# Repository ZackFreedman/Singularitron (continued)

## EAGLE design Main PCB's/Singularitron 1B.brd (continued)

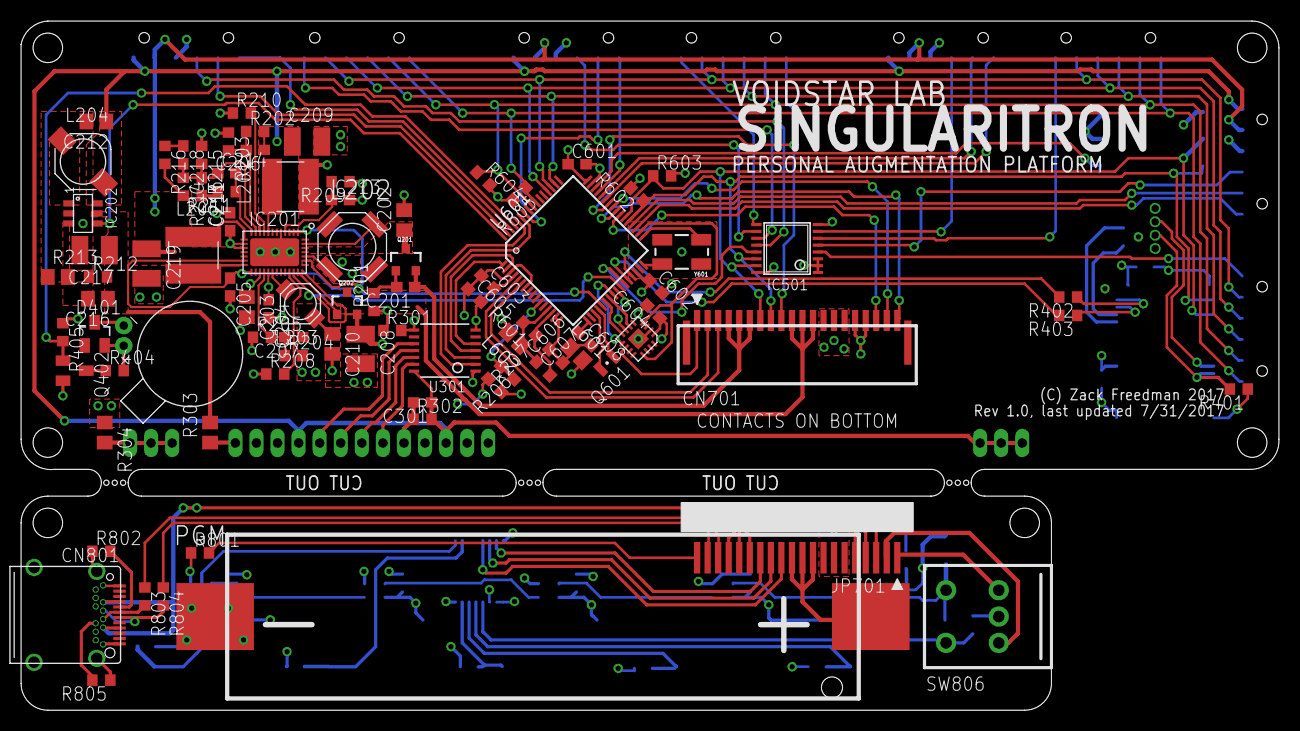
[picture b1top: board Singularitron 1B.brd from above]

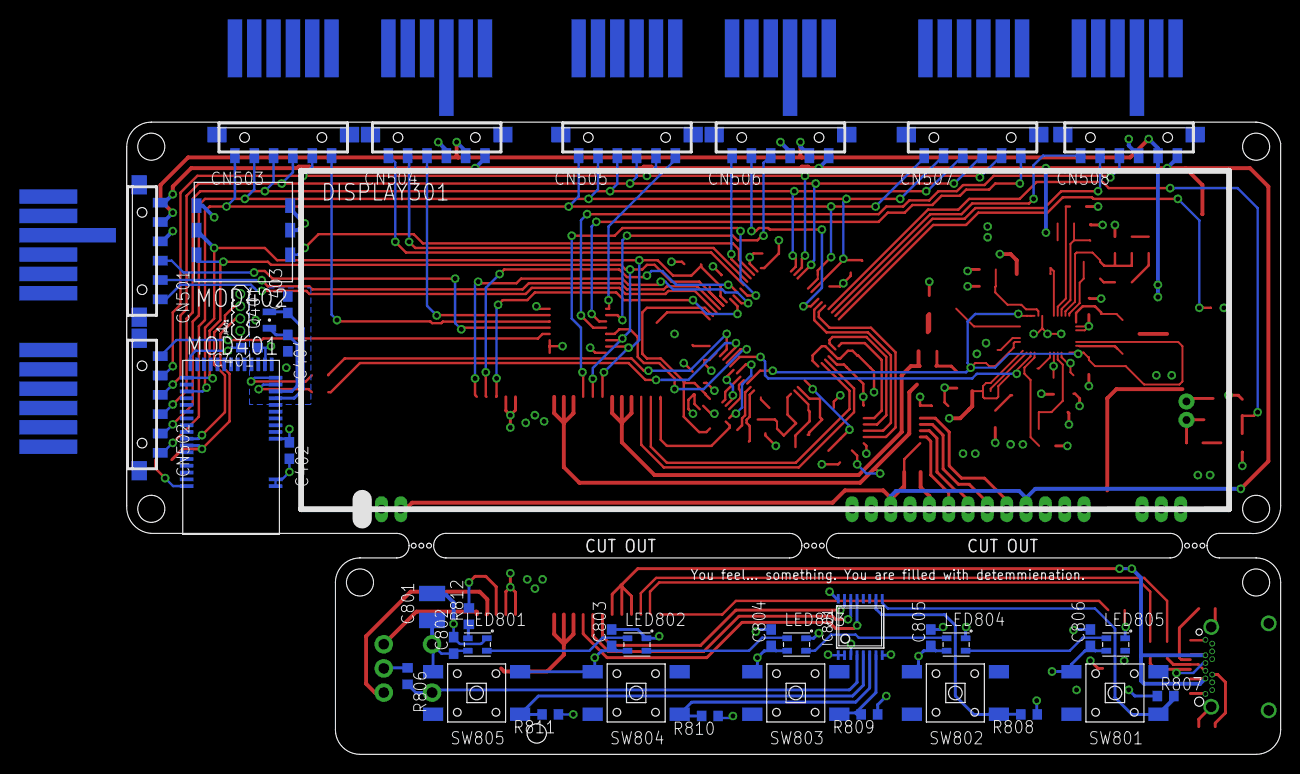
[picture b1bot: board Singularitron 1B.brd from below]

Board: 4 copper layers, 119.4 x 65.4 mm, 133 parts (41 on the bottom side), 126 nets.

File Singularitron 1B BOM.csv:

"Qty";"Value";"Device";"Package";"Parts";"Description";"";
"1";"";"FFC_1MM_20POS_DIRECT";"FFC_1MM_20POS_DIRECT";"JP701";"1mm-pitch, 20-position FFC glued and soldered directly to the PCB.";"";
"1";"";"M041.27MM";"1X04-1.27MM";"JP401";"Header 4";"";
"1";"";"TXB0104PWR";"TSSOP14";"U301";"4-Bit Bi-Directional Level Shifter";"";
"1";"0.01µF";"C-USC0603";"C0603";"C301";"CAPACITOR, American symbol";"";
"12";"0.1µF";"C-USC0603";"C0603";"C213, C601, C602, C603, C604, C607, C608, C802, C803, C804, C805, C806";"CAPACITOR, American symbol";"";
"1";"0.47µH";"C-USC1210";"C1210";"C217";"CAPACITOR, American symbol";"";
"1";"100nF";"C-USC0603";"C0603";"C201";"CAPACITOR, American symbol";"";
"1";"100Ω";"R-US_R0603";"R0603";"R812";"RESISTOR, American symbol";"";
"2";"105kΩ";"R-US_R0603";"R0603";"R205, R215";"RESISTOR, American symbol";"";
"10";"10kΩ";"R-US_R0603";"R0603";"R207, R210, R301, R405, R806, R807, R808, R809, R810, R811";"RESISTOR, American symbol";"";
"1";"10kΩ 0.1% 250mW";"R-US_R0805";"R0805";"R213";"RESISTOR, American symbol";"";
"3";"10pF";"C-USC0603";"C0603";"C206, C207, C214";"CAPACITOR, American symbol";"";
"3";"10µF";"C-USC0805";"C0805";"C202, C203, C210";"CAPACITOR, American symbol";"";
"1";"121kΩ";"R-US_R0603";"R0603";"R216";"RESISTOR, American symbol";"";
"1";"12401548E4#2A";"12401548E4#2A";"12401548E4#2A";"CN801";"Amphenol USB C receptacle, surface-mount and through-hole pins";"";
"1";"12kΩ";"R-US_R0603";"R0603";"R401";"RESISTOR, American symbol";"";
"2";"12pF";"C-USC0603";"C0603";"C403, C404";"CAPACITOR, American symbol";"";
"1";"15kΩ";"R-US_R0603";"R0603";"R211";"RESISTOR, American symbol";"";
"1";"16.9kΩ";"R-US_R0603";"R0603";"R203";"RESISTOR, American symbol";"";
"1";"16MHz";"CRYSTAL-SHIELDED";"CRYSTAL-SMD-5X3";"Y601";"";"";
"1";"1MΩ";"R-US_R0603";"R0603";"R801";"RESISTOR, American symbol";"";
"1";"1kΩ";"R-US_R0603";"R0603";"R208";"RESISTOR, American symbol";"";
"4";"1µF";"C-USC0603";"C0603";"C204, C205, C401, C402";"CAPACITOR, American symbol";"";
"1";"1µF";"C-USC0805";"C0805";"C212";"CAPACITOR, American symbol";"";
"3";"2.2µF";"C-USC0603";"C0603";"C211, C605, C606";"CAPACITOR, American symbol";"";
"2";"2.2µH";"CDRH4D22/HP";"CDRH4D22/HP";"L201, L205";"Sumida low-DCR shielded inductor";"";
"1";"200kΩ";"R-US_R0603";"R0603";"R302";"RESISTOR, American symbol";"";
"2";"220Ω";"R-US_R0603";"R0603";"R402, R403";"RESISTOR, American symbol";"";
"1";"22pF";"C-USC0805";"C0805";"C216";"CAPACITOR, American symbol";"";
"4";"22µH";"C-USC1210";"C1210";"C208, C209, C219, C801";"CAPACITOR, American symbol";"";
"1";"22µH";"SUMIDA_CDPH4D19F";"CDPH4D19F";"L204";"Low-profile shielded inductor, proprietary footprint, useful for low-current switching regulators";"";
"1";"22Ω";"R-US_R0603";"R0603";"R404";"RESISTOR, American symbol";"";
"1";"22Ω 1/2W?";"R-US_R0805";"R0805";"R303";"RESISTOR, American symbol";"";
"1";"280kΩ 0.1%";"R-US_R0603";"R0603";"R212";"RESISTOR, American symbol";"";
"1";"3.01kΩ";"R-US_R0603";"R0603";"R209";"RESISTOR, American symbol";"";
"1";"3.3µH";"CDRH6D12";"CDRH6D12";"L202";"Sumida low-profile shielded inductor";"";
"1";"3.61kΩ";"R-US_R0603";"R0603";"R206";"RESISTOR, American symbol";"";
"2";"324kΩ";"R-US_R0603";"R0603";"R204, R214";"RESISTOR, American symbol";"";
"1";"32kHz";"FC-12M";"FC-12M";"Q401";"kHz RANGE CRYSTAL UNIT";"";
"1";"32kHz 12pF";"FC-12M";"FC-12M";"Q601";"kHz RANGE CRYSTAL UNIT";"";
"1";"330pF";"C-USC0603";"C0603";"C215";"CAPACITOR, American symbol";"";
"1";"33pF";"C-USC0603";"C0603";"C218";"CAPACITOR, American symbol";"";
"2";"33Ω";"R-US_R0603";"R0603";"R803, R804";"RESISTOR, American symbol";"";
"4";"4.7kΩ";"R-US_R0603";"R0603";"R602, R603, R604, R605";"RESISTOR, American symbol";"";
"1";"4.7µH";"CDRH3D16/HP";"CDRH3D16/HP";"L203";"Sumida miniature low-profile shielded inductor";"";
"1";"40kΩ";"R-US_R0603";"R0603";"R201";"RESISTOR, American symbol";"";
"1";"470Ω";"R-US_R0603";"R0603";"R601";"RESISTOR, American symbol";"";
"2";"5.1kΩ";"R-US_R0603";"R0603";"R802, R805";"RESISTOR, American symbol";"";
"1";"6.2Ω 1/2W";"R-US_R0805";"R0805";"R304";"RESISTOR, American symbol";"";
"2";"600Ω@100MHz";"FERRITE-0603";"FB603";"L601, L602";"Ferrite bead in various packages";"";
"1";"88.7kΩ";"R-US_R0603";"R0603";"R202";"RESISTOR, American symbol";"";
"8";"AVX_9155066";"AVX_9155066";"9155006";"CN501, CN502, CN503, CN504, CN505, CN506, CN507, CN508";"AVX 6-position 2mm pitch right-angle battery connector";"";
"1";"BAT54C";"BAT54C";"SOT23";"D401";"Schottky Diodes";"";
"1";"DS2045";"DS2045";"DS2045";"DISPLAY301";"";"";
"1";"EM7180SFP";"EM7180SFP";"EM7180SFP";"MOD402";"EM7180SFP Sensor fusion platform module. Incorporated EM7180 Sentral Hub coprocessor, Bosch BMX055 9-DOF IMU, and ST24256 32KB EEPROM.";"";
"1";"HFW20R-1ST";"HFW20R-1ST";"HFW20R-1STE1LF";"CN701";"Amphenol HF20R 20-contact 1mm-pitch FFC/FPC connector. No locking feature - friction only.";"";
"1";"KEYSTONE_1024";"KEYSTONE_1024";"KEYSTONE-1024-PROVISIONAL";"BAT801";"";"";
"1";"LT3461A";"LT3461A";"SOT-23";"IC202";"Linear Technologies LT3461A 3MHz boost regulator, 16V max VIN, 38V max VOUT, 70mA output load current";"";
"1";"LTC3586-3";"LTC3586-3";"QFN-38_EP_UFE";"IC201";"Linear LTC3586 PMIC";"";
"1";"MDBT40";"MDBT40";"MDBT40";"MOD401";"";"";
"1";"MK20DX128VLH5";"MK20DX128VLH5";"MK20DX128VLH5";"U601";"Teensy 3.0 Processing Unit - MK20DX128VLH5 ARM Cortex M0";"";
"1";"MKL02Z32VFG4";"MKL02Z32VFG4";"QFN16-3X3";"IC601";"";"";
"1";"MOTOR10MM";"MOTOR10MM";"VIBE-MOTOR-10MM";"MOTOR401";"Vibration Motor- ROB-08449";"";
"5";"NEOPIXEL_NANO_2427";"NEOPIXEL_NANO_2427";"SK6805-2427";"LED801, LED802, LED803, LED804, LED805";"";"";
"1";"NVR4003NT3G";"MOSFET-NREFLOW";"SOT23";"Q402";"N-Channel Mosfet";"";
"2";"PCA9534PW";"PCA9534PW";"TSSOP16";"IC501, IC801";"8-bit I2C-bus and SMBus low power I/O port with interrupt";"";
"1";"PEC09";"PEC09";"PEC09-2X20X-TXXXX";"SW806";"Bourns low-profile rotary encoders";"";
"2";"SI2333DS-T1-E3";"MOSFET-PCHANNELSMD";"SOT23-3";"Q201, Q202";"Generic PMOSFET";"";
"4";"SINGULARITRON_CART_BASE";"SINGULARITRON_CART_BASE";"SINGULARITRON_CART_BASE";"JP501, JP502, JP503, JP504";"";"";
"5";"TACTILE_SWITCHTL3301-G";"TACTILE_SWITCHTL3301-G";"TL3301-X-FXXX-X-G";"SW801, SW802, SW803, SW804, SW805";"";"";

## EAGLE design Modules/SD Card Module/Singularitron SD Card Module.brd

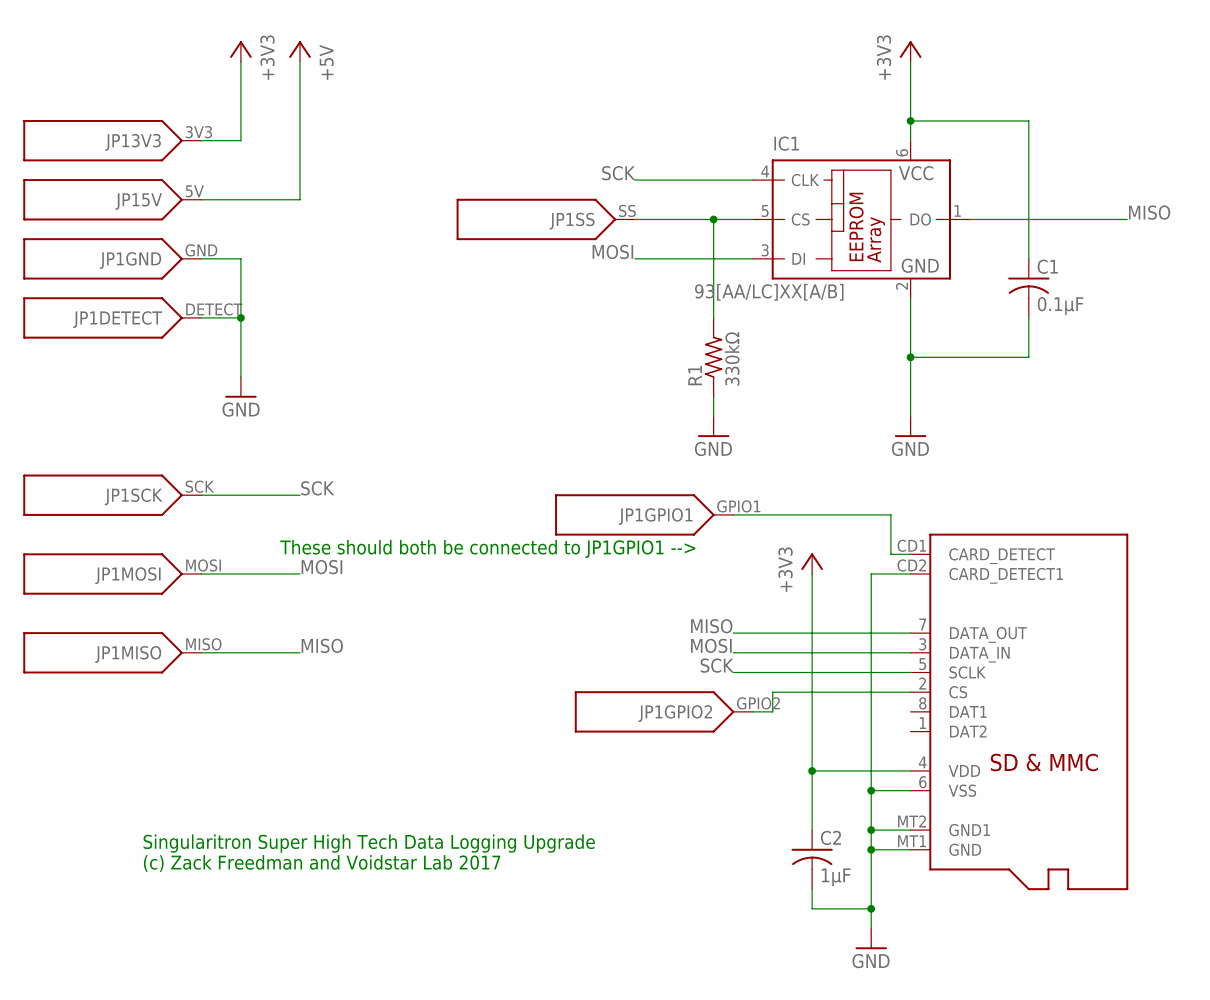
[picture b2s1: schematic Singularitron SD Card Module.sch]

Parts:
C1: 0.1µF; C0603
C2: 1µF; C0603
IC1: 93[AA/LC]XX[A/B]; SOT23-6
JP1: SINGULARITRON_CART_BASE
JP2: MICROSD
R1: 330kΩ; R0603

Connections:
+3V3: C1.1, C2.1, IC1.6 (VCC), JP1.3V3, JP2.4 (VDD)
+5V: JP1.5V
GND: C1.2, C2.2, IC1.2 (GND), JP1.DETECT, JP1.GND, JP2.6 (VSS), JP2.CD2 (CARD_DETECT1), JP2.MT1 (GND), JP2.MT2 (GND1), R1.1
MISO: IC1.1 (DO), JP1.MISO, JP2.7 (DATA_OUT)
MOSI: IC1.3 (DI), JP1.MOSI, JP2.3 (DATA_IN)
unnamed: IC1.5 (CS), JP1.SS, R1.2
unnamed: JP1.GPIO1, JP2.CD1 (CARD_DETECT)
unnamed: JP1.GPIO2, JP2.2 (CS)
SCK: IC1.4 (CLK), JP1.SCK, JP2.5 (SCLK)

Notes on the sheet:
Singularitron Super High Tech Data Logging Upgrade (c) Zack Freedman and Voidstar Lab 2017
These should both be connected to JP1GPIO1 -->

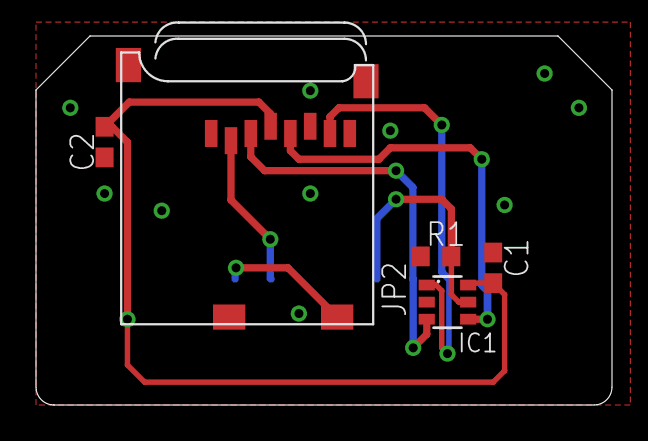
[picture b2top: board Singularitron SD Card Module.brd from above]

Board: 2 copper layers, 32.0 x 20.5 mm, 6 parts (0 on the bottom side), 8 nets.

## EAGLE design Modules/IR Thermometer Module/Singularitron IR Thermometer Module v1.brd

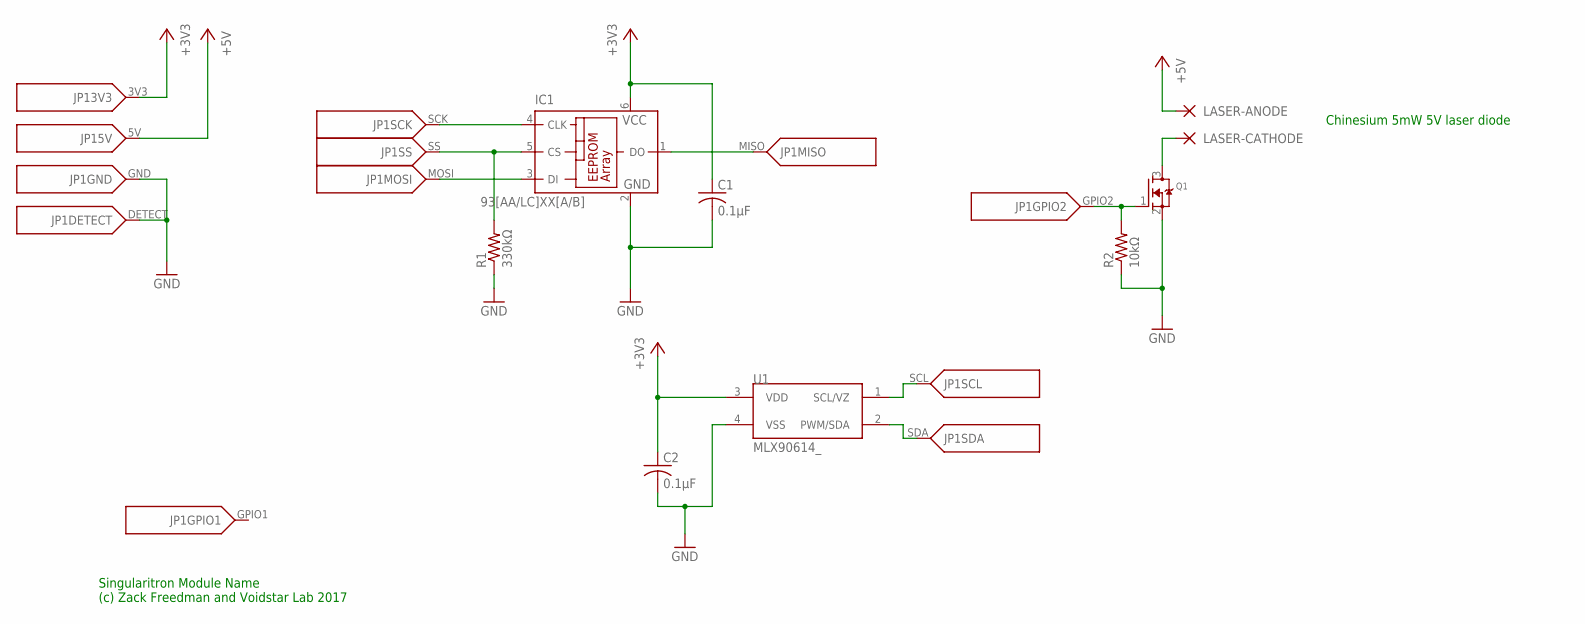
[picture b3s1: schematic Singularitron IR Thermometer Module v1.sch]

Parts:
C1, C2: 0.1µF; C0603
IC1: 93[AA/LC]XX[A/B]; SOT23-6
JP1: SINGULARITRON_CART_BASE
LASER-ANODE: 1,6/0,9
LASER-CATHODE: 1,6/0,9
Q1: MOSFET-NREFLOW; SOT23
R1: 330kΩ; R0603
R2: 10kΩ; R0603
U1: MLX90614_; TO-39

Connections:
+3V3: C1.1, C2.1, IC1.6 (VCC), JP1.3V3, U1.3 (VDD)
+5V: JP1.5V, LASER-ANODE.1
GND: C1.2, C2.2, IC1.2 (GND), JP1.DETECT, JP1.GND, Q1.2 (S), R1.1, R2.1, U1.4 (VSS)
LASER: JP1.GPIO2, Q1.1 (G), R2.2
unnamed: IC1.5 (CS), JP1.SS, R1.2
unnamed: JP1.SCL, U1.1 (SCL/VZ)
unnamed: JP1.SDA, U1.2 (PWM/SDA)
unnamed: LASER-CATHODE.1, Q1.3 (D)
unnamed: IC1.4 (CLK), JP1.SCK
unnamed: IC1.3 (DI), JP1.MOSI
unnamed: IC1.1 (DO), JP1.MISO

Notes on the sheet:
Singularitron Module Name (c) Zack Freedman and Voidstar Lab 2017
Chinesium 5mW 5V laser diode

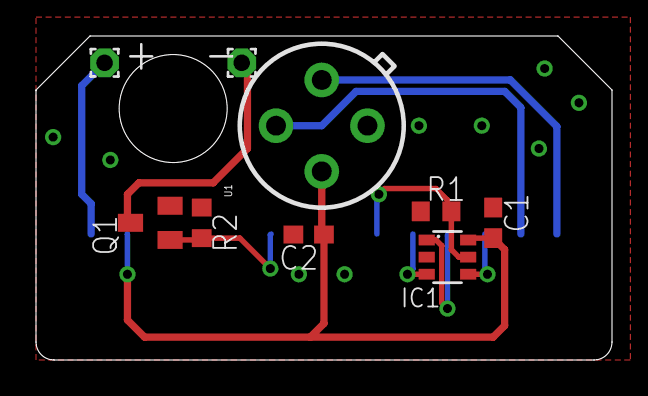
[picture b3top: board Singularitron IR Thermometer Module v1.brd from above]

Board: 4 copper layers, 32.0 x 18.0 mm, 10 parts (0 on the bottom side), 11 nets.

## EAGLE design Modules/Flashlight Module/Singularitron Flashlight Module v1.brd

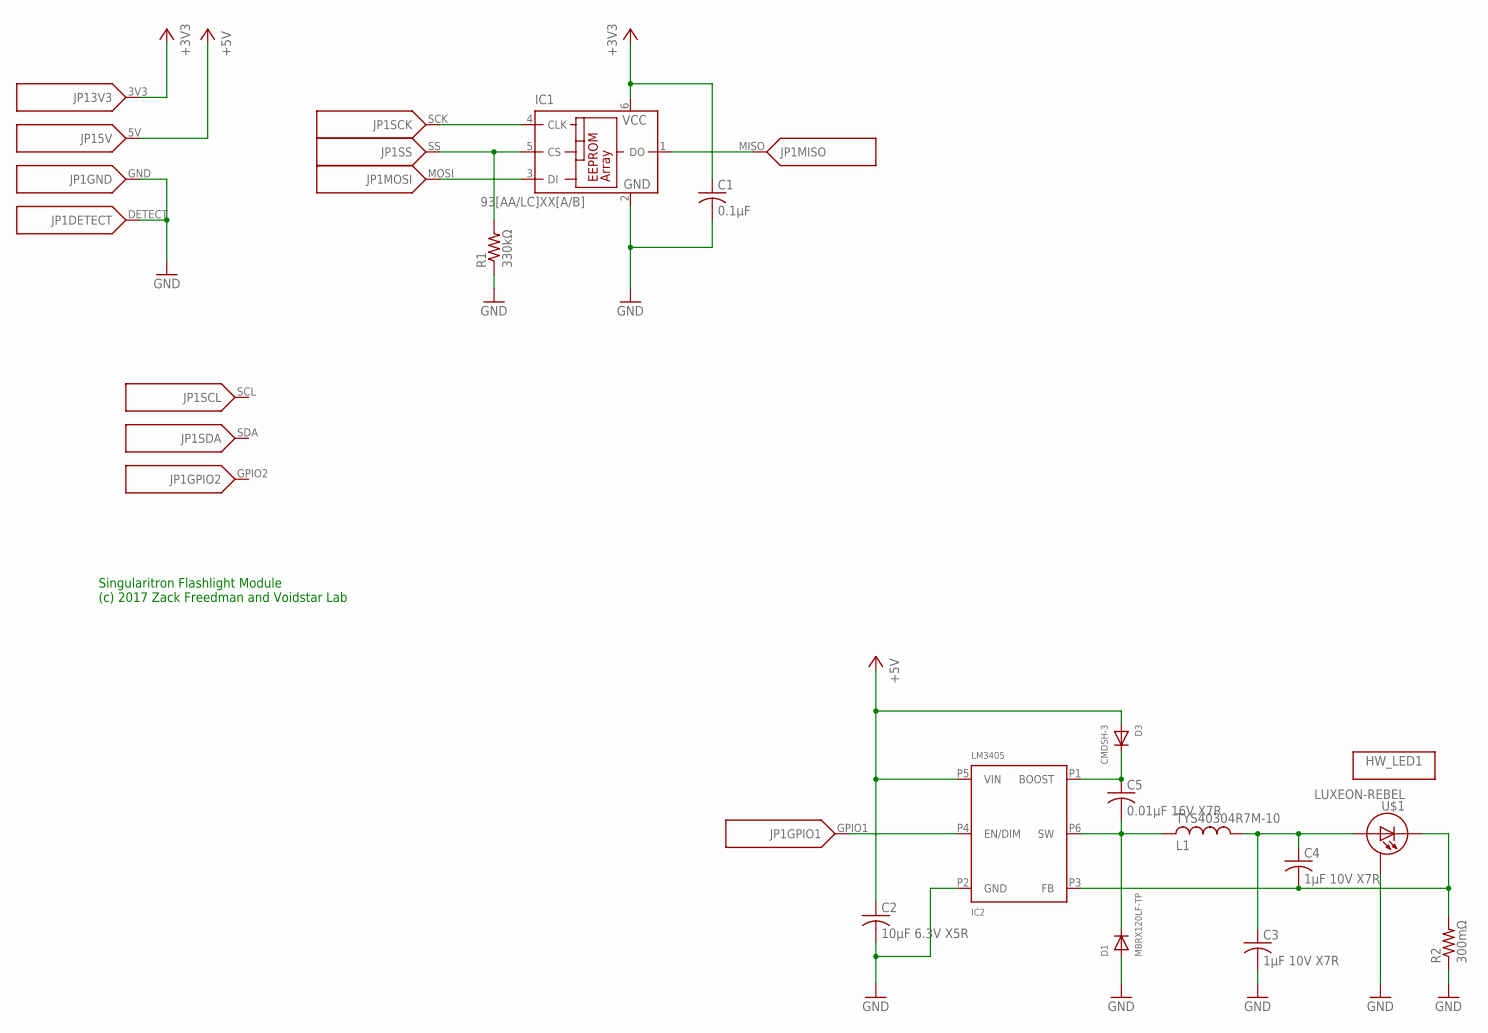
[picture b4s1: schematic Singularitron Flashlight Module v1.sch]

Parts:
C1: 0.1µF; C0603
C2: 10µF 6.3V X5R; C0805
C3, C4: 1µF 10V X7R; C0805
C5: 0.01µF 16V X7R; C0603
D1: MBRX120LF-TP; SOD-123
D3: CMDSH-3; SOD-323F
HW_LED1: CARCLO_10771_10772; CARCLO_10MM_NARROW_MEDIUM
IC1: 93[AA/LC]XX[A/B]; SOT23-6
IC2: LM3405; SOT-23
JP1: SINGULARITRON_CART_BASE
L1: TYS40304R7M-10
R1: 330kΩ; R0603
R2: 300mΩ; R0805
U$1: LUXEON-REBEL

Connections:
+3V3: C1.1, IC1.6 (VCC), JP1.3V3
+5V: C2.1, D3.A, IC2.P5 (VIN), JP1.5V
GND: C1.2, C2.2, C3.2, D1.A, IC1.2 (GND), IC2.P2 (GND), JP1.DETECT, JP1.GND, R1.1, R2.1, U$1.P$3 (S)
unnamed: IC1.5 (CS), JP1.SS, R1.2
unnamed: IC1.4 (CLK), JP1.SCK
unnamed: IC1.3 (DI), JP1.MOSI
unnamed: IC1.1 (DO), JP1.MISO
unnamed: IC2.P4 (EN/DIM), JP1.GPIO1
unnamed: C5.1, D3.C, IC2.P1 (BOOST)
unnamed: C5.2, D1.C, IC2.P6 (SW), L1.P$2 (2)
unnamed: C3.1, C4.1, L1.P$1 (1), U$1.ANODE (A)
unnamed: C4.2, IC2.P3 (FB), R2.2, U$1.CATHODE (C)

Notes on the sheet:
Singularitron Flashlight Module (c) 2017 Zack Freedman and Voidstar Lab

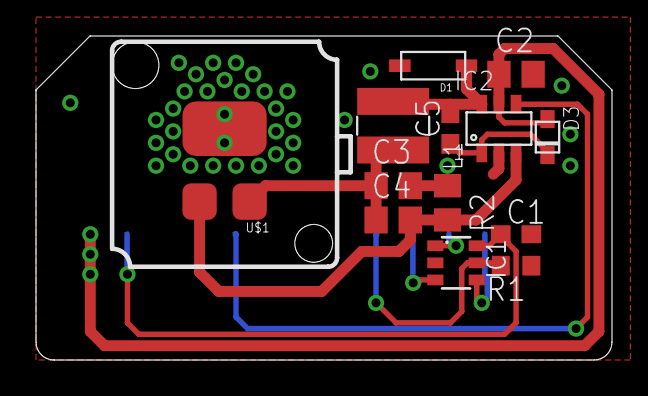
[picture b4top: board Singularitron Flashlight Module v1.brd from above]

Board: 2 copper layers, 32.0 x 18.0 mm, 15 parts (0 on the bottom side), 12 nets.

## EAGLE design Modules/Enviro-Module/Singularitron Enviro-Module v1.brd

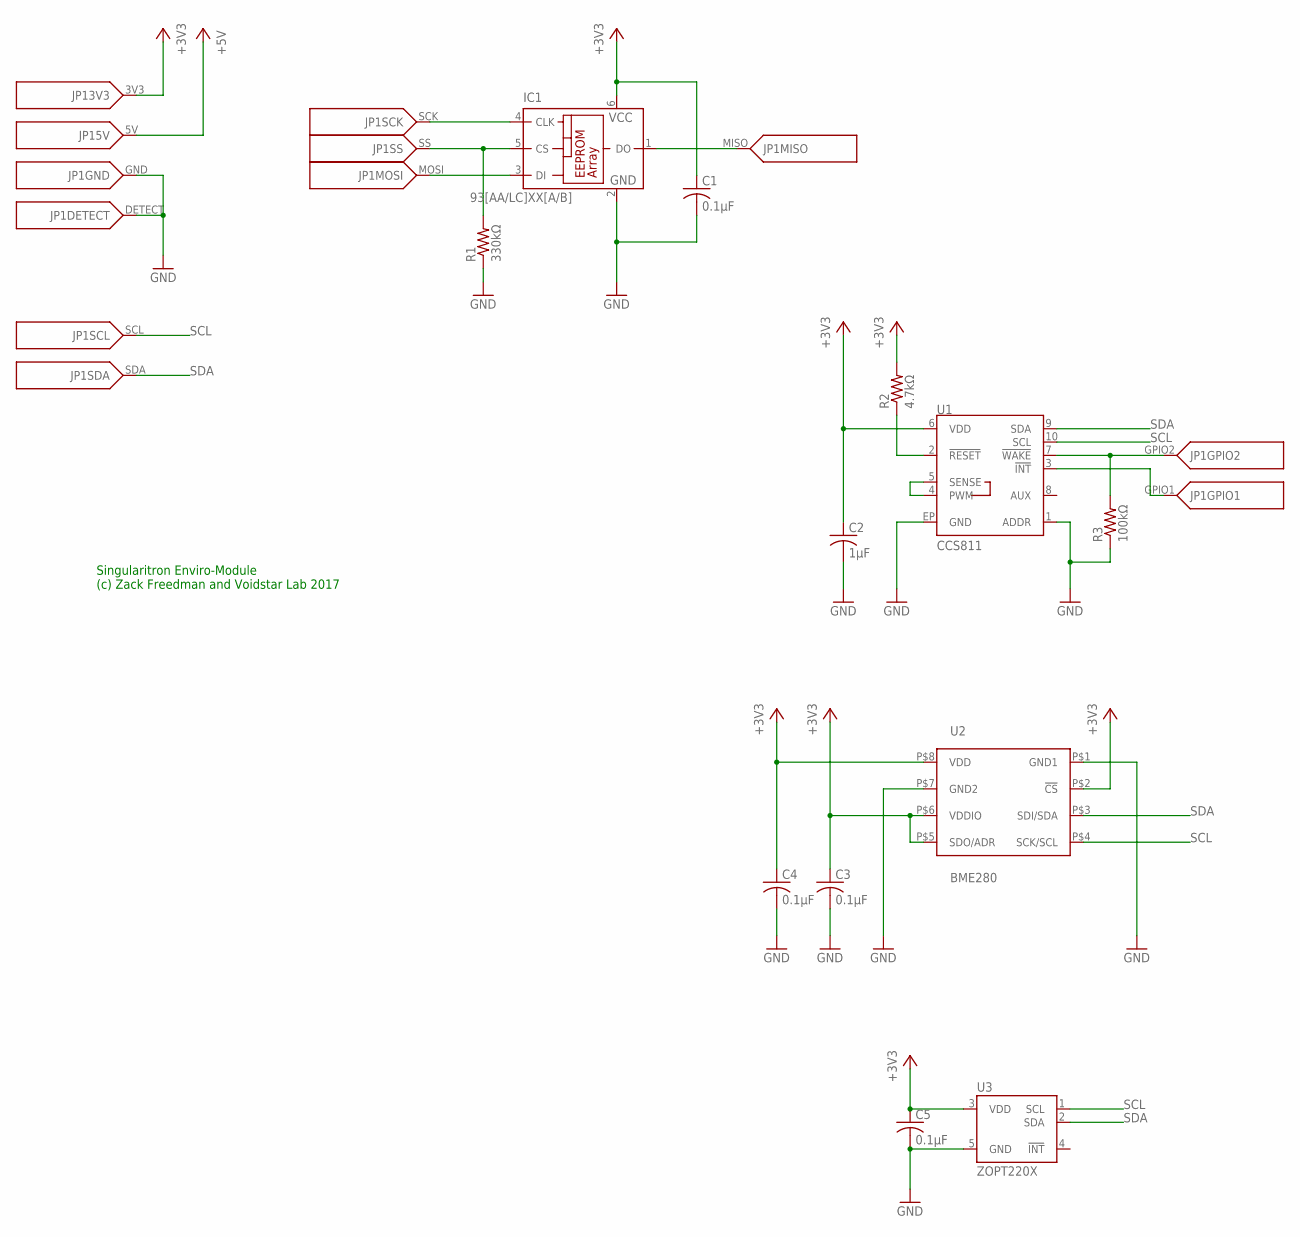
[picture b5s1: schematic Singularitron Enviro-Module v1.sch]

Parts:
C1, C3, C4, C5: 0.1µF; C0603
C2: 1µF; C0603
IC1: 93[AA/LC]XX[A/B]; SOT23-6
JP1: SINGULARITRON_CART_BASE
R1: 330kΩ; R0603
R2: 4.7kΩ; R0603
R3: 100kΩ; R0603
U1: CCS811; LGA10
U2: BME280; BME280_LGA
U3: ZOPT220X; LGA6

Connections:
+3V3: C1.1, C2.1, C3.1, C4.1, C5.1, IC1.6 (VCC), JP1.3V3, R2.2, U1.6 (VDD), U2.P$2 (!CS), U2.P$5 (SDO/ADR), U2.P$6 (VDDIO), U2.P$8 (VDD), U3.3 (VDD)
+5V: JP1.5V
GND: C1.2, C2.2, C3.2, C4.2, C5.2, IC1.2 (GND), JP1.DETECT, JP1.GND, R1.1, R3.1, U1.1 (ADDR), U1.EP (GND), U2.P$1 (GND1), U2.P$7 (GND2), U3.5 (GND)
unnamed: IC1.5 (CS), JP1.SS, R1.2
unnamed: IC1.4 (CLK), JP1.SCK
unnamed: IC1.3 (DI), JP1.MOSI
unnamed: IC1.1 (DO), JP1.MISO
unnamed: R2.1, U1.2 (!RESET!)
unnamed: JP1.GPIO2, R3.2, U1.7 (!WAKE!)
unnamed: JP1.GPIO1, U1.3 (!INT!)
unnamed: U1.4 (PWM), U1.5 (SENSE)
SCL: JP1.SCL, U1.10 (SCL), U2.P$4 (SCK/SCL), U3.1 (SCL)
SDA: JP1.SDA, U1.9 (SDA), U2.P$3 (SDI/SDA), U3.2 (SDA)

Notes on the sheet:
Singularitron Enviro-Module (c) Zack Freedman and Voidstar Lab 2017

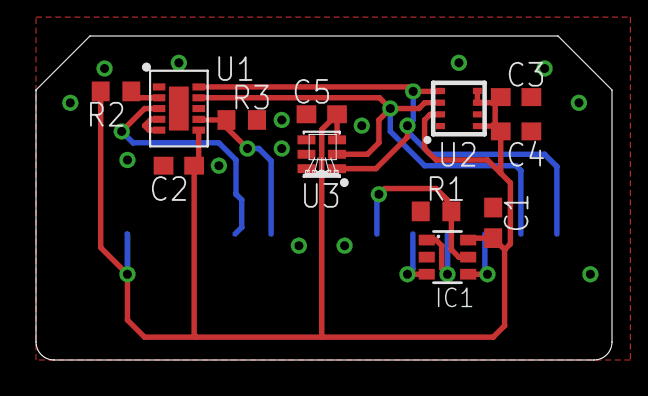
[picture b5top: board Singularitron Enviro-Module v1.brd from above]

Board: 2 copper layers, 32.0 x 18.0 mm, 13 parts (0 on the bottom side), 12 nets.

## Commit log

2020-01-06 Added all the files
    Accidentally created the repo INSIDE the project folder instead of WITH it.
    Don't judge, you probably did it too.
2020-01-06 Added some stuff to the readme
2020-01-06 Added modified VFD libraries
2020-01-06 Added 3D design files
2021-06-07 Added some pics of the main unit PCB layout
2021-06-07 More Cartridges!!!
    Major overhaul done in preparation for the Singularitron episode!
    - Implemented breathalyzer, fluxgate, light sensor, OLED, and pulse oximeter cartridges
    - No code for Teensy module, I ran out of time
    - Pulse ox is EXTREMELY slow and buggy. Oximeter functionality is faked for now - this bug prevents the system from collecting data fast enough for sensible readings
    - Added system app for infinite boot messages
2021-06-07 Added way, way too many flavor text elements
    Also spoiler alert for this episode's Co-Lab-Orator Easter egg
